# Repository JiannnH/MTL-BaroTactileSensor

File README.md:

# MTL-BaroTactileSensor

This repository contains the code and hardware design for the research project titled "Superresolution of a Barometric Tactile Sensor." The project is being conducted as part of an MSc Thesis at Imperial College London, which is continually updating.

# Project Description
The objective of this project is to develop an integrated tactile sensor solution based on traditional barometers to produce a more precise and sophisticated tactile output. The project encompasses the entire development cycle, including PCB design, hardware design, data collection, and deep learning model training.

The primary focus of the project is on enhancing the resolution of tactile sensors using machine learning techniques.

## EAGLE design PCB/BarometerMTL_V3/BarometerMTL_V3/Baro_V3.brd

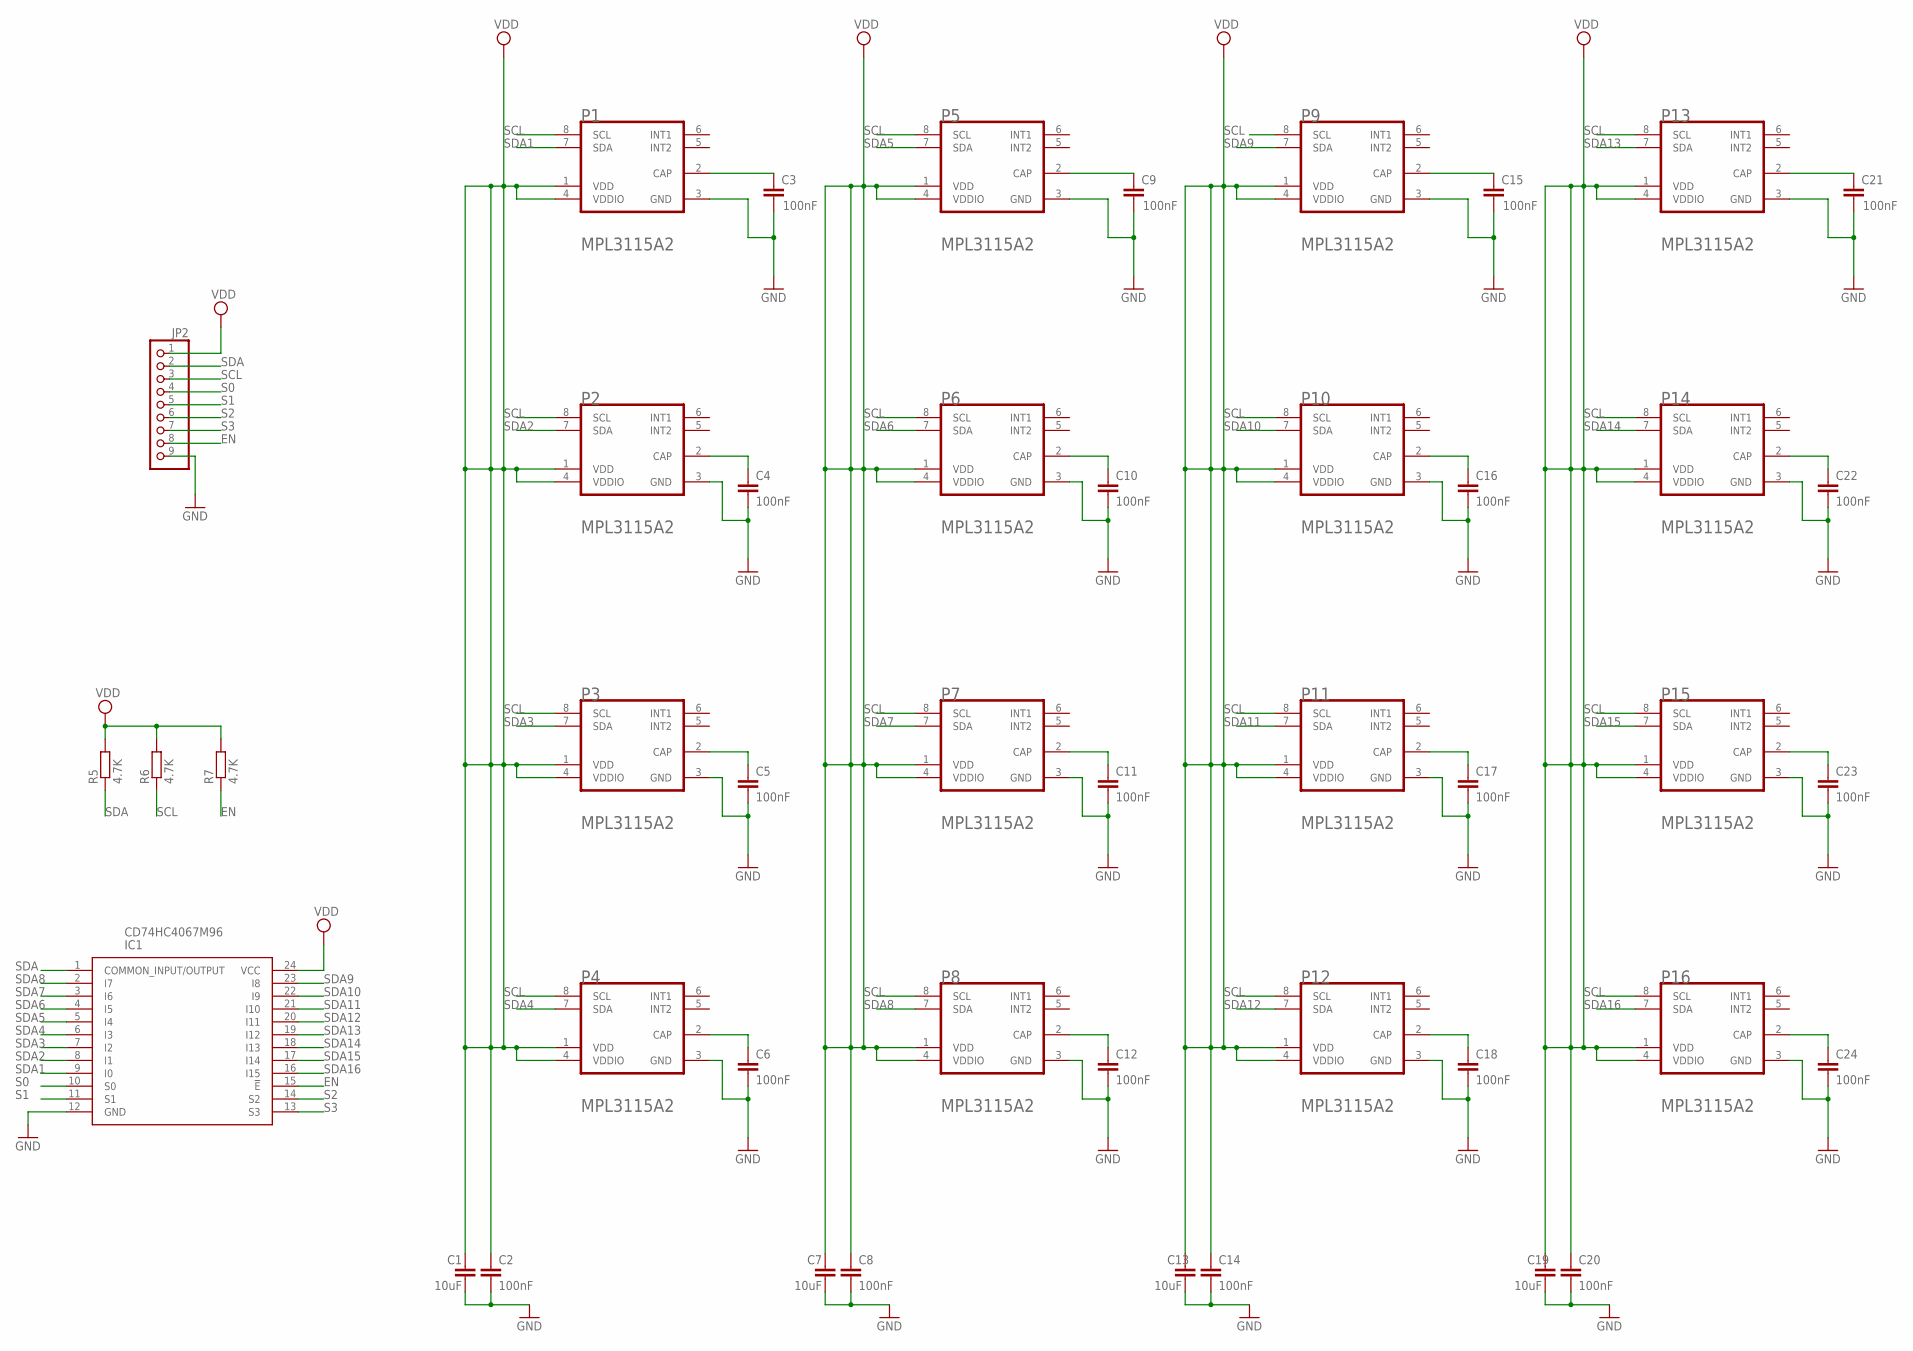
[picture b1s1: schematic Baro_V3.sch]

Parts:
C1, C7, C13, C19: 10uF; C0603
C2, C3, C4, C5, C6, C8, C9, C10, C11, C12, C14, C15, C16, C17, C18, C20, C21, C22, C23, C24: 100nF; C0805
IC1: CD74HC4067M96; SOIC127P1030X265-24N
JP2: PINHD-1X9; 1X09
P1, P2, P3, P4, P5, P6, P7, P8, P9, P10, P11, P12, P13, P14, P15, P16: FREESCALE_SEMICONDUCTOR_MPL3115A2FREESCALE_SEMICO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; FREESCALE_SEMICONDUCTOR_MPL3115A2_0
R5, R6, R7: 4.7K; R0603

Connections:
EN: IC1.15 (!E), JP2.8, R7.1
GND: C1.2, C2.2, C3.2, C4.2, C5.2, C6.2, C7.2, C8.2, C9.2, C10.2, C11.2, C12.2, C13.2, C14.2, C15.2, C16.2, C17.2, C18.2, C19.2, C20.2, C21.2, C22.2, C23.2, C24.2, IC1.12 (GND), JP2.9, P1.3 (GND), P2.3 (GND), P3.3 (GND), P4.3 (GND), P5.3 (GND), P6.3 (GND), P7.3 (GND), P8.3 (GND), P9.3 (GND), P10.3 (GND), P11.3 (GND), P12.3 (GND), P13.3 (GND), P14.3 (GND), P15.3 (GND), P16.3 (GND)
unnamed: C3.1, P1.2 (CAP)
unnamed: C4.1, P2.2 (CAP)
unnamed: C9.1, P5.2 (CAP)
unnamed: C10.1, P6.2 (CAP)
unnamed: C11.1, P7.2 (CAP)
unnamed: C12.1, P8.2 (CAP)
unnamed: C5.1, P3.2 (CAP)
unnamed: C6.1, P4.2 (CAP)
unnamed: C15.1, P9.2 (CAP)
unnamed: C16.1, P10.2 (CAP)
unnamed: C17.1, P11.2 (CAP)
unnamed: C18.1, P12.2 (CAP)
unnamed: C21.1, P13.2 (CAP)
unnamed: C22.1, P14.2 (CAP)
unnamed: C23.1, P15.2 (CAP)
unnamed: C24.1, P16.2 (CAP)
S0: IC1.10 (S0), JP2.4
S1: IC1.11 (S1), JP2.5
S2: IC1.14 (S2), JP2.6
S3: IC1.13 (S3), JP2.7
SCL: JP2.3, P1.8 (SCL), P2.8 (SCL), P3.8 (SCL), P4.8 (SCL), P5.8 (SCL), P6.8 (SCL), P7.8 (SCL), P8.8 (SCL), P9.8 (SCL), P10.8 (SCL), P11.8 (SCL), P12.8 (SCL), P13.8 (SCL), P14.8 (SCL), P15.8 (SCL), P16.8 (SCL), R6.1
SDA: IC1.1 (COMMON_INPUT/OUTPUT), JP2.2, R5.1
SDA1: IC1.9 (I0), P1.7 (SDA)
SDA2: IC1.8 (I1), P2.7 (SDA)
SDA3: IC1.7 (I2), P3.7 (SDA)
SDA4: IC1.6 (I3), P4.7 (SDA)
SDA5: IC1.5 (I4), P5.7 (SDA)
SDA6: IC1.4 (I5), P6.7 (SDA)
SDA7: IC1.3 (I6), P7.7 (SDA)
SDA8: IC1.2 (I7), P8.7 (SDA)
SDA9: IC1.23 (I8), P9.7 (SDA)
SDA10: IC1.22 (I9), P10.7 (SDA)
SDA11: IC1.21 (I10), P11.7 (SDA)
SDA12: IC1.20 (I11), P12.7 (SDA)
SDA13: IC1.19 (I12), P13.7 (SDA)
SDA14: IC1.18 (I13), P14.7 (SDA)
SDA15: IC1.17 (I14), P15.7 (SDA)
SDA16: IC1.16 (I15), P16.7 (SDA)
VDD: C1.1, C2.1, C7.1, C8.1, C13.1, C14.1, C19.1, C20.1, IC1.24 (VCC), JP2.1, P1.1 (VDD), P1.4 (VDDIO), P2.1 (VDD), P2.4 (VDDIO), P3.1 (VDD), P3.4 (VDDIO), P4.1 (VDD), P4.4 (VDDIO), P5.1 (VDD), P5.4 (VDDIO), P6.1 (VDD), P6.4 (VDDIO), P7.1 (VDD), P7.4 (VDDIO), P8.1 (VDD), P8.4 (VDDIO), P9.1 (VDD), P9.4 (VDDIO), P10.1 (VDD), P10.4 (VDDIO), P11.1 (VDD), P11.4 (VDDIO), P12.1 (VDD), P12.4 (VDDIO), P13.1 (VDD), P13.4 (VDDIO), P14.1 (VDD), P14.4 (VDDIO), P15.1 (VDD), P15.4 (VDDIO), P16.1 (VDD), P16.4 (VDDIO), R5.2, R6.2, R7.2

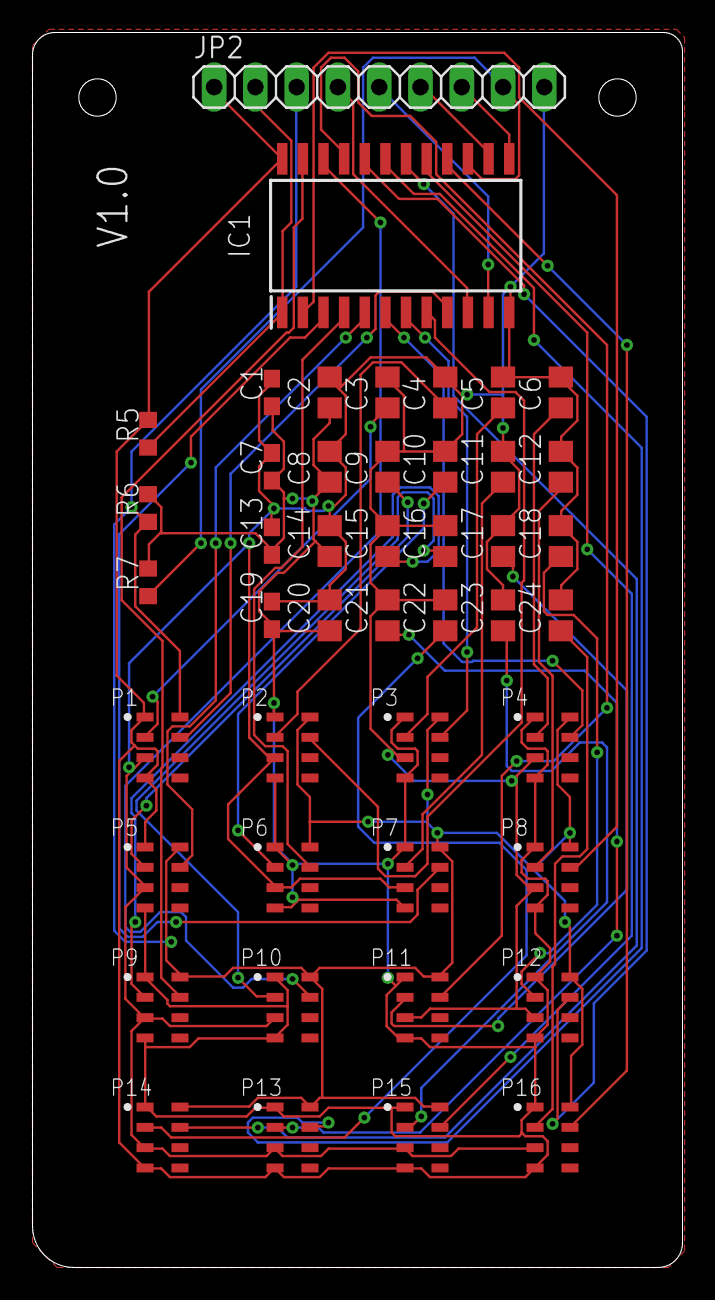
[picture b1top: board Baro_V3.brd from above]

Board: 2 copper layers, 40.0 x 76.0 mm, 45 parts (0 on the bottom side), 41 nets.

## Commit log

2023-07-13 upload
